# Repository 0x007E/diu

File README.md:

# `DIU` - Digital (Analog) Clock (Digitaluhr)

The `DIU` project is based on a pcb with an [ATtiny1606](#additional-information) a RTC [MCP7940](#additional-information) a USB/UART bridge [FT232RL](#additional-information) and a set of [74HC595](#additional-information) shift register. It can be used to display time and date on 84 `LEDs` that are mounted in 3 circles to the top pcb. The clock itself can be setup over UART and a terminal software ([e.g. TeraTerm](#additional-information)).

| Experience | Level |
|:------------|:-----:|
| Soldering   |  |
| Mechanical  |  |
| Software    |  |

# Downloads

| Type      | File               | Description              |
|:---------:|:------------------:|:-------------------------|
| Schematic | [pdf](https://github.com/0x007E/diu/releases/latest/download/schematic.pdf) / [cadlab](https://cadlab.io/project/28616/main/files) | Schematic files |
| Board | [pdf](https://github.com/0x007E/diu/releases/latest/download/pcb.pdf) / [cadlab](https://cadlab.io/project/28616/main/files) | Board file |
| Drill | [pdf](https://github.com/0x007E/diu/releases/latest/download/drill.pdf) | Drill file |
| PCB | [zip](https://github.com/0x007E/diu/releases/latest/download/kicad.zip) / [tar](https://github.com/0x007E/diu/releases/latest/download/kicad.tar.gz) | KiCAD/Gerber/BoM/Drill files |
| Mechanical | [zip](https://github.com/0x007E/diu/releases/latest/download/freecad.zip) / [tar](https://github.com/0x007E/diu/releases/latest/download/freecad.tar.gz) | FreeCAD/Housing and PCB (STEP) files     |
| Firmware | [zip](https://github.com/0x007E/diu/releases/latest/download/firmware.zip) / [tar](https://github.com/0x007E/diu/releases/latest/download/firmware.tar.gz) | Firmware for ATtiny1606 |
| Test-Firmware | [zip](https://github.com/0x007E/diu/releases/latest/download/test-firmware.zip) / [tar](https://github.com/0x007E/diu/releases/latest/download/test-firmware.tar.gz) | Test-Firmware for ATtiny1606 |

# Hardware

There are two parts of the hardware. The pcb and the housing of the `DIU`. The pcb is created with [KiCAD](#additional-information) and the housing with [FreeCAD](#additional-information). The software is programmed with [Microchip (Atmel) Studio](#additional-information). All files are built with `github actions` so that they are ready for a production environment. The housing is printed with a 3D-printer (`Dremel 3D40`).

## PCB

The circuit board is populated on both sides (Top, Bottom). The best way for soldering the `SMD` components is within a vapor phase soldering system and for the `THT` components with a standard soldering system. After placing and soldering the top parts, the board has to be cut off in the middle (white edge).

### Top Layer

### Bottom Layer

## Mechanical

The housing has a tolerance of `0.2mm` on each side of the case. So the pcb should fit perfectly in the housing. The tolerance can be modified with `FreeCAD` in the `Parameter` Spreadsheet. The corners of the circuit board need to be sanded a little.

### Assembled

#### Exploded

# Programming/Setup

The `DIU` can be powerd with `5V` from USB or an external source through connector `J1`. Over [UPDI](#additional-information) (`J3`) the `DIU` can be programmed with `avr-dude` or an [Microchip (Atmel) ICE](#additional-information) adapter. To setup the `DIU` it can be connected over USB to a computer and  configured with a terminal (e.g. [TeraTerm](#additional-information)) software. The firmware for the clock can be downloaded from the [download section](#downloads).

## FUSES

| Register  | Value  |
|:---------:|:------:|
| `WDTCFG`  | `0x00` |
| `BODCFG`  | `0x00` |
| `OSCCFG`  | `0x02` |
| `TCD0CFG` | `0x00` |
| `SYSCFG0` | `0xF5` |
| `SYSCFG1` | `0x00` |
| `APPEND`  | `0x00` |
| `BOOTEND` | `0x00` |

> To setup `RESET` (`PA0`) it is necessary to change the `SYSCFG0`-FUSE of the `ATtiny1606`. WARNING: To reset the `PA0` pin to `UPDI` mode a `12V` impulse is necessary to program the FUSES again.

# Firmware

The firmware of the `DIU` project can be downloaded and modified with [Microchip Studio](#additional-information). The software can be found in the [`./firmware`](./firmware/) directory and is splitted into different libraries. They can be found in the [./firmware/lib`](./firmware/lib/) folder. Feel free to modify the firmware to your own needings.

## Dataflow diagram

## UART Setup

To configure the `DIU` through UART (USB/UART bridge) a connection over USB to a computer and a terminal software (e.g. [Teraterm](#additional-information) is necessary. To start the setup the following settings need to be configured in the terminal. Then hit a key during init process in the terminal.

| Name      | Value  |
|:---------:|:------:|
| PORT      | COM?   |
| BAUD      | 9600   |
| DATABITS  | 8      |
| PARITY    | NONE   |
| STOPBITS  | 1      |
| FLOWCTRL  | NONE   |

### Connection setup

``` bash
# +--------------------------------------------------+
# |       ~------------------+                       |      +---------------------+
# |      ~  ATTINY 1606      |                       |      |                     |
# |     ~                  +-+-+                     |      | +-----------------+ |
# |    ~               VCC | 1 |          +----------+      | | TeraTerm        | |
# |      ~             PB0 | 2 |          |   U  +---+---+  | | ~~~~~~~~        | |
# |        ~           PB1 | 3 |          |   S  |  USB  |--+ | ~~~~~           | |
# |         ~    (TxD) PB2 | 4 +-----+    |   B  +---+---+  | | ~~~~~~~~~~~~    | |
# |        ~     (RxD) PB3 | 5 +--+  |    |   /      |      | |                 | |
# |       ~            GND | 6 |  |  |    |   U      |      | +-----------------+ |
# |     ~                  +-+-+  |  |    |   A      |      |                     |
# |    ~~~~~-----------------+    |  |  +-+-+ R      |      | Computer            |
# |                               |  +--+TxD| T      |      |                     |
# |  DDD   IIIIII UU  UU          +-----+RxD| +------+      +---------------------+
# |  D  D    II   UU  UU                +-+-+ |5V/3V3|
# |  D  D    II   UU  UU                  +----+-----+
# |  DDD   IIIIII  UUUU                              |
# +--------------------------------------------------+
```

### Enter configuration menu

To enter into the configuration mode it is necessary to press a `key` during startup.

The configuration starts and a menu to setup the `DIU` appears.

``` bash
# +------------------------------------------------+
# | System Configuration                           |
# +------------------------------------------------+
# | [1] Time and Date                              |
# | [2] Alarm                                      |
# | [3] Alarm Tone                                 |
# | [4] LED Intensity                              |
# | [5] Oscillator                                 |
# | [d] Discharge changes                          |
# | [q] Exit configuration                         |
# +------------------------------------------------+
# Input:
```

## TWI-Configuration

The `DIU` itself uses a `RTC` ([MCP7940](#additional-information)) with a power reserve (`battery`) to store the time. The `firmware` is connecte to the `RTC` over `TWI`. The twi configuration is stored in [`twi.h`](./firmware/lib/twi/twi.h) and the rtc configuration in [`mcp7940.h`](./firmware/lib/rtc/mcp7940.h) file.

### Connection between `ATtiny1606` and `MCP7940`

``` bash
# +----------------------------------------------------------------------------------------------------+
# |                               VCC VCC                                                              |
# |                                ^   ^                                                               |
# |                                |   |                                                               |
# |                             R +++ +++ R                                                            |
# |                             9 | | | | 1                                                            |
# |       ~------------------+  9 | | | | 0                                J                           |
# |      ~  ATTINY 1606      |    +++ +++ 0    +---------------------+     1    ~~~~~~                 |
# |     ~                  +-+-+   |   |     +-+-+                 +-+-+   8   ~  3   ~                |
# |    ~               VCC | X +---|---|-----+ 8 | VCC         BAT | 3 +--(X)-+   V    +------| GND    |
# |    ~         (SCL) PB0 | 0 +---+---|-----+ 6 | SCL             +-+-+       ~  0   ~                |
# |     ~        (SDA) PB1 | 1 +-------+-----+ 5 | SDA      M        |          ~~~~~~   C30           |
# |       ~            PB2 | 2 |             +-+-+          C      +-+-+                 ||            |
# |        ~           PB3 | 3 |           +-+ 5 | MFP      P   X! | 1 +----------+------||----| GND   |
# |         ~          PB4 | 4 |          /  +-+-+          7      +-+-+         ---     ||            |
# |         ~          PB5 | 5 |         /     |            9        |         +-----+                 |
# |        ~           PB6 | 6 |        /    +-+-+          4        |         |  Y1 | 32.768 kHz      |
# |       ~            GND | X +-------/-----+ 4 |          0        |         +-----+                 |
# |      ~                 +-+-+      /      +-+-+                 +-+-+         ---     ||            |
# |     ~                    |       /         |                X2 | 2 +----------+------||----| GND   |
# |     ~                  +-+-+    /          |                   +-+-+                 ||            |
# |      ~                 ~   ~   /           +---------------------+                   C31           |
# |       ~                ~   ~  /                                                                    |
# |        ~           PA7 | 7 +-+             DDD   IIIIII UU  UU                                     |
# |         ~              +-+-+               D  D    II   UU  UU                                     |
# |         ~                |                 D  D    II   UU  UU                                     |
# |        ~-----------------+                 DDD   IIIIII  UUUU                                      |
# +----------------------------------------------------------------------------------------------------+
```

### TWI Parameter

To read and save parameters in th `RTC` over `TWI` the bus is configured with the following setup:

| Parameter | Value   | Description     |
|:----------|:-------:|:----------------|
| Speed     | 400kHz  | Bus clock speed |

> Detail can be found [here](https://en.wikipedia.org/wiki/I%C2%B2C)

### RTC-Commands

``` c
             void mcp7940_init(RTC_Mode battery);
             void mcp7940_battery(RTC_Mode mode);
             void mcp7940_oscillator(RTC_Mode mode);

    unsigned char mcp7940_oscillator_value(void);
             void mcp7940_oscillator_copy(Copy_Mode mode);

       RTC_Status mcp7940_powerfail_status(void);
       RTC_Status mcp7940_oscillator_status(void);

      const char* mcp7940_weekday_string(unsigned char day);
    
    unsigned char mcp7940_hour(RTC_Data data);
    unsigned char mcp7940_minute(RTC_Data data);
    unsigned char mcp7940_second(void);

    unsigned char mcp7940_weekday(RTC_Data data);
    unsigned char mcp7940_day(RTC_Data data);
    unsigned char mcp7940_month(RTC_Data data);
    unsigned char mcp7940_year(void);
    unsigned char mcp7940_leapyear(void);

       RTC_Status mcp7940_setweekday(unsigned char weekday);
       RTC_Status mcp7940_settime(unsigned char hour, unsigned char minute, unsigned char second);
       RTC_Status mcp7940_setdate(unsigned char day, unsigned char month, unsigned char year);
       RTC_Status mcp7940_setoscillator(unsigned char trim);
```

## SPI-Configuration

The `firmware` itself is driving the LEDs over `SPI` through eleven [74HC595](#additional-information) shift registers. The spi configuration is stored in the [`clock.h`](./firmware/lib/clock/clock.h) and [`spi.h`](./firmware/lib/spi/spi.h) files.

### Connection between `ATtiny1606` and `74HC595`

``` bash
# +------------------------------------------------------------------------------------------------------+
# |                                     +----------------------------... ~ ...------------------------+  |
# |       ~------------------+         /            START(1)            ~             END(11)         |  | 
# |      ~  ATTINY 1606      |        /        +---------------+       ~         +---------------+    |  |
# |     ~                  +-+-+     /       +-+-+  74HC595  +-+-+    ~        +-+-+  74HC595  +-+-+  |  |
# |    ~               VCC | X +----/--------+ 16|    VCC    |16 |-.. ~ ....---+ 16|    VCC    |16 |  |  |
# |    ~               PA0 | 0 |   /         +---+           +-+-+     ~       +---+           +-+-+  |  |
# |     ~       (MOSI) PA1 | 1 +--/----------+ 14| SER    QH | 9 |--... ~ ...--+ 14| SER    QH | 9 +--+  |
# |       ~     (MISO) PA2 | 2 +-+           +---+           +-+-+       ~     +---+           +-+-+     |
# |        ~     (SCK) PA3 | 3 +-------------+ 11|   SRCLK   |11 |----... ~ ..-+ 11|   SRCLK   |11 |     |
# |         ~     (SS) PA4 | 4 +-------------+ 12|    RCLK   |12 |----... ~ ..-+ 12|    RCLK   |12 |     |
# |         ~  (CLEAR) PA5 | 5 +-------------+ 10|   SRCLR   |10 |---... ~ ...-+ 10|   SRCLR   |10 |     |
# |        ~  (OUTPUT) PA6 | 6 +-------------+ 13|     OE    |13 |--... ~ ...--+ 13|     OE    |13 |     |
# |       ~            GND | X +-------------+ 8 |    GND    | 8 |-... ~ ...---+ 8 |    GND    | 8 |     |
# |     ~                  +-+-+             +-+-+           +-+-+    ~        +-+-+           +-+-+     |
# |    ~~~~~-----------------+                 +--+~~~~~~~~~+--+      ~          +--+~~~~~~~~~+--+       |
# |                                               |         |          ~            |         |          |
# |  DDD   IIIIII UU  UU                         ---  LED  ---          ~          ---  LED  ---         |   
# |  D  D    II   UU  UU                         \ /       \ /           ~         \ /       \ /         |
# |  D  D    II   UU  UU                          |         |             ~         |         |          |
# |  DDD   IIIIII  UUUU                           |         |             ~         |         |          |
# +------------------------------------------------------------------------------------------------------+
```

### SPI Parameter

To control the LEDs through the shift registers over `SPI` the bus is configured with the following setup:

| Parameter | Value   | Description |
|:----------|:-------:|:------------|
| Clock     | F_CPU/4 | Bus clock speed is system speed divied by 4 |
| Direction | MSB     | MSB needs to be transmitted first |
| Polarity  | Rising  | Polarity of clock is rising `_/` |
| Phase     | Rising  | Data is valid when clock is rising `_/` |

> Detail can be found [here](https://de.wikipedia.org/wiki/Serial_Peripheral_Interface)

### SPI Frame

``` bash

# SPI display transmission
# _                                                SS                                                   _
#  \__________________________________________________~~~______________________________________________/
#                                                 SCK   
#     __    __    __    __    __    __    __    __       __    __    __    __    __    __    __    __    
# ___/1 \__/2 \__/3 \__/4 \__/5 \__/6 \__/7 \__/8 \__~~~/81\__/82\__/83\__/84\__/85\__/86\__/87\__/88\___
#                                                 MOSI
#    __    __    __    __    __    __    __    __       __    __    __    __    __    __    __    __
# __/H \__/O \__/U \__/R \__/  \__/  \__/  \__/  \__~~~/M \__/I \__/N \__/  \__/L3\__/L2\__/L1\__/L0\____
#   \__/  \__/  \__/  \__/  \__/  \__/  \__/  \__/     \__/  \__/  \__/  \__/  \__/  \__/  \__/  \__/
#    [7                   :                    0]    [7                   :                    0]
#
# L[3:0] ... LEDs on the backside of the pcb for signaling
```

### Clock-Commands

``` c
           void clock_init(void);
           void clock_output(CLOCK_Status status);
           void clock_clear(void);
   unsigned int clock_intensity(void);
    CLOCK_Error clock_setintensity(unsigned int intensity);
           void clock_copy_intensity(Copy_Mode mode);
    CLOCK_Error clock_settime(unsigned char hour, unsigned char minute, unsigned char second, CLOCK_Status_LED status);
    CLOCK_Error clock_setdate(unsigned char day, unsigned char month, CLOCK_Status_LED status);
           void clock_setdata(unsigned long data24, unsigned long long data60, CLOCK_Status_LED status);
           void clock_saveintensity(void);
```

# Additional Information

| Type       | Link               | Description              |
|:----------:|:------------------:|:-------------------------|
| ATtiny1606 | [pdf](http://ww1.microchip.com/downloads/en/DeviceDoc/ATtiny806_1606_Data_Sheet_40002029A.pdf) | ATtiny microcontroller |
| MPC7940 | [pdf](https://ww1.microchip.com/downloads/aemDocuments/documents/MPD/ProductDocuments/DataSheets/MCP7940N-Battery-Backed-I2C-RTCC-with-SRAM-20005010J.pdf) | Battery-Backed I2C Real-Time Clock/Calendar with SRAM |
| FT232RL | [pdf](https://ftdichip.com/wp-content/uploads/2020/08/DS_FT232R.pdf) | USB Full Speed to Serial UART IC, Includes Oscillator and EEPROM |
| 74HC595 | [pdf](https://www.ti.com/lit/ds/symlink/sn74hc595.pdf?) | 8-Bit Shift Registers With 3-State Output Registers |
| Atmel ICE | [pdf](https://ww1.microchip.com/downloads/en/DeviceDoc/Atmel-ICE_UserGuide.pdf) | Atmel ICE datasheet |
| UPDI | [web](https://github.com/0x007e/updi) | UPDI-Adapter with AVR-Dude |
| Microchip Studio | [web](https://www.microchip.com/en-us/tools-resources/develop/microchip-studio) | Download page for Microchip Studio |
| KiCAD | [web](https://www.kicad.org/) | KiCAD project page |
| FreeCAD | [web](https://www.freecad.org/) | FreeCAD project page |
| TeraTerm | [web](https://github.com/TeraTermProject/teraterm/releases/download/v5.3/teraterm-5.3.zip) | Terminal software for UART |

---

R. GAECHTER

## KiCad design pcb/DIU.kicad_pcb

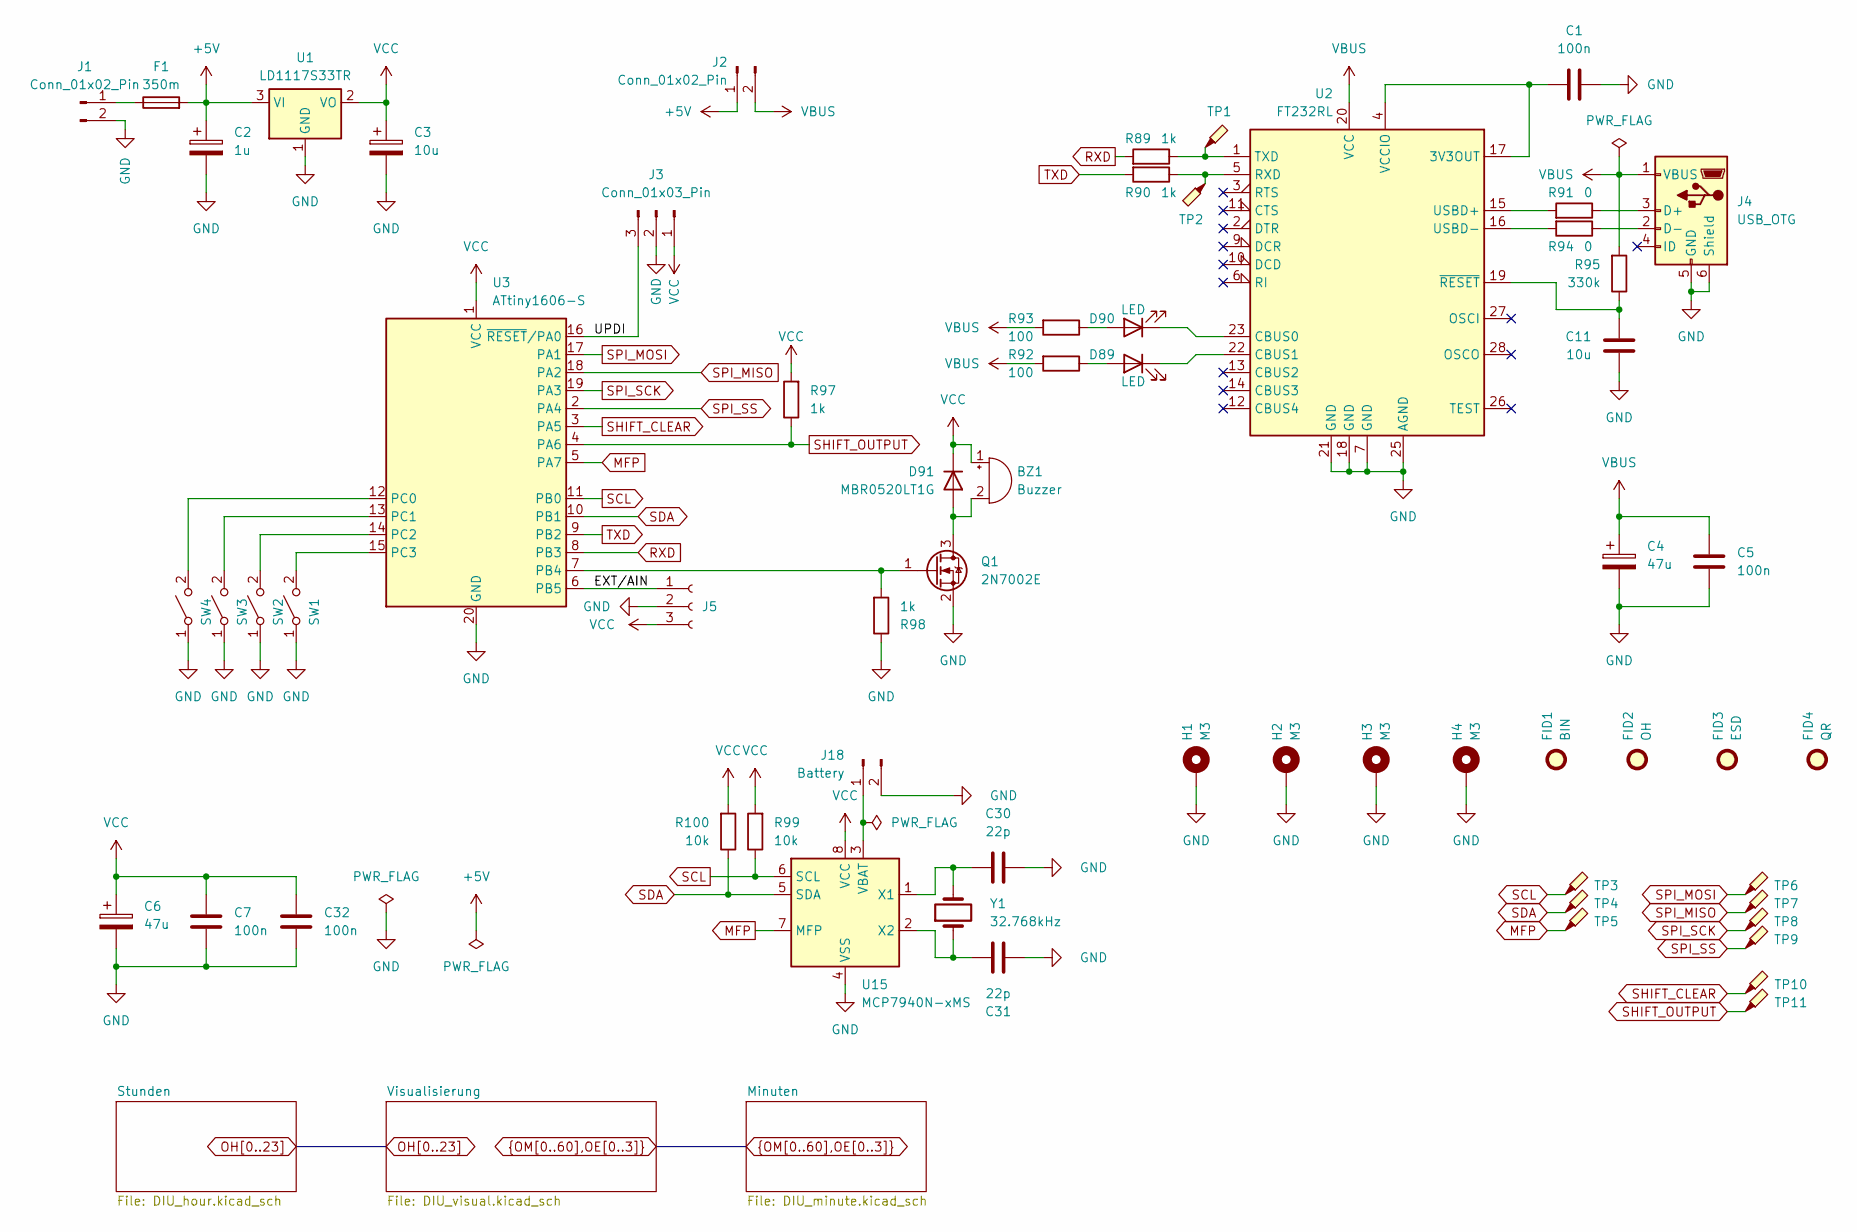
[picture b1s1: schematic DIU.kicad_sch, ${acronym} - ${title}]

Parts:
BZ1: Buzzer; MagneticBuzzer_ProSignal_ABT-410-RC
C1, C32: 100n; C_0603_1608Metric
C2: 1u; CP_EIA-3528-21_Kemet-B
C3: 10u; CP_EIA-6032-28_Kemet-C
C4, C6: 47u; CP_EIA-6032-15_Kemet-U
C5, C7: 100n; C_1206_3216Metric
C11: 10u; C_0603_1608Metric
C30, C31: 22p; C_0603_1608Metric
D89, D90: LED; LED_0603_1608Metric
D91: MBR0520LT1G; D_SOD-123
F1: 350m; Fuse_1206_3216Metric_Pad1.42x1.75mm_HandSolder
FID1: BIN; WEEE-Logo_4.2x6mm_SilkScreen
FID2: OH; OSHW-Logo2_7.3x6mm_SilkScreen
FID3: ESD; ESD-Logo_6.6x6mm_SilkScreen
FID4: QR; QR_0x007e
H1, H2, H3, H4: M3; MountingHole_3.2mm_M3_DIN965_Pad
J1, J2: Conn_01x02_Pin; PinHeader_1x02_P2.54mm_Vertical
J3: Conn_01x03_Pin; PinHeader_1x03_P2.54mm_Vertical
J4: USB_OTG; USB_Mini-B_Tensility_54-00023_Vertical
J5: Conn_01x03_Socket; PinSocket_1x03_P2.54mm_Vertical
J18: Battery; BatteryHolder_LINX_BAT-HLD-012-SMT
Q1: 2N7002E; SOT-23
R89, R90: 1k; R_0603_1608Metric
R91, R94: 0; R_0603_1608Metric
R92, R93: 100; R_0603_1608Metric
R95: 330k; R_0603_1608Metric
R97, R98: 1k; R_1206_3216Metric
R99, R100: 10k; R_0603_1608Metric
SW1, SW2, SW3, SW4: SW_SPST; SW_SPST_PTS645
TP1, TP2, TP3, TP4, TP5, TP6, TP7, TP8, TP9, TP10, TP11: TestPoint_Probe; TestPoint_Pad_D1.0mm
U1: LD1117S33TR; TO-263-2
U2: FT232RL; SSOP-28_5.3x10.2mm_P0.65mm
U3: ATtiny1606-S; SOIC-20W_7.5x12.8mm_P1.27mm
U15: MCP7940N-xMS; SOIC-8_3.9x4.9mm_P1.27mm
Y1: 32.768kHz; Crystal_SMD_3215-2Pin_3.2x1.5mm

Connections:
+5V: C2.1, F1.2, J2.1, U1.3 (VI)
/EXT/AIN: J5.1, U3.6 (PB5)
/UPDI: J3.3, U3.16 (~RESET/PA0)
GND: C1.2, C2.2, C3.2, C4.2, C5.2, C6.2, C7.2, C11.1, C30.2, C31.2, C32.2, H1.1, H2.1, H3.1, H4.1, J1.2, J3.2, J4.5 (GND), J4.6 (Shield), J5.2, J18.2, Q1.2 (S), R98.1, SW1.1 (A), SW2.1 (A), SW3.1 (A), SW4.1 (A), U1.1 (GND), U2.7 (GND), U2.18 (GND), U2.21 (GND), U2.25 (AGND), U3.20 (GND), U15.4 (VSS); also elsewhere on the board
MFP: TP5.1, U3.5 (PA7), U15.7 (MFP)
unnamed: BZ1.2 (-), D91.2 (A), Q1.3 (D)
unnamed: D89.2 (A), R92.1
unnamed: D89.1 (K), U2.22 (CBUS1)
unnamed: D90.2 (A), R93.1
unnamed: D90.1 (K), U2.23 (CBUS0)
unnamed: F1.1, J1.1
unnamed: J4.3 (D+), R91.1
unnamed: J4.2 (D-), R94.1
unnamed: J18.1, U15.3 (VBAT)
unnamed: Q1.1 (G), R98.2, U3.7 (PB4)
unnamed: SW1.2 (B), U3.15 (PC3)
unnamed: SW2.2 (B), U3.14 (PC2)
unnamed: SW3.2 (B), U3.13 (PC1)
unnamed: SW4.2 (B), U3.12 (PC0)
unnamed: C1.1, U2.4 (VCCIO), U2.17 (3V3OUT)
unnamed: R90.1, TP2.1, U2.5 (RXD)
unnamed: R89.1, TP1.1, U2.1 (TXD)
unnamed: R91.2, U2.15 (USBD+)
unnamed: R94.2, U2.16 (USBD-)
unnamed: C11.2, R95.1, U2.19 (~RESET)
unnamed: C30.1, U15.1 (X1), Y1.2
unnamed: C31.1, U15.2 (X2), Y1.1
RXD: R89.2, U3.8 (PB3)
SCL: R99.1, TP3.1, U3.11 (PB0), U15.6 (SCL)
SDA: R100.1, TP4.1, U3.10 (PB1), U15.5 (SDA)
SHIFT_CLEAR: TP10.1, U3.3 (PA5); also elsewhere on the board
SHIFT_OUTPUT: R97.1, TP11.1, U3.4 (PA6); also elsewhere on the board
SPI_MISO: TP7.1, U3.18 (PA2); also elsewhere on the board
SPI_MOSI: TP6.1, U3.17 (PA1); also elsewhere on the board
SPI_SCK: TP8.1, U3.19 (PA3); also elsewhere on the board
SPI_SS: TP9.1, U3.2 (PA4); also elsewhere on the board
TXD: R90.2, U3.9 (PB2)
VBUS: C4.1, C5.1, J2.2, J4.1 (VBUS), R92.2, R93.2, R95.2, U2.20 (VCC)
VCC: BZ1.1 (+), C3.1, C6.1, C7.1, C32.1, D91.1 (K), J3.1, J5.3, R97.2, R99.2, R100.2, U1.2 (VO), U3.1 (VCC), U15.8 (VCC); also elsewhere on the board

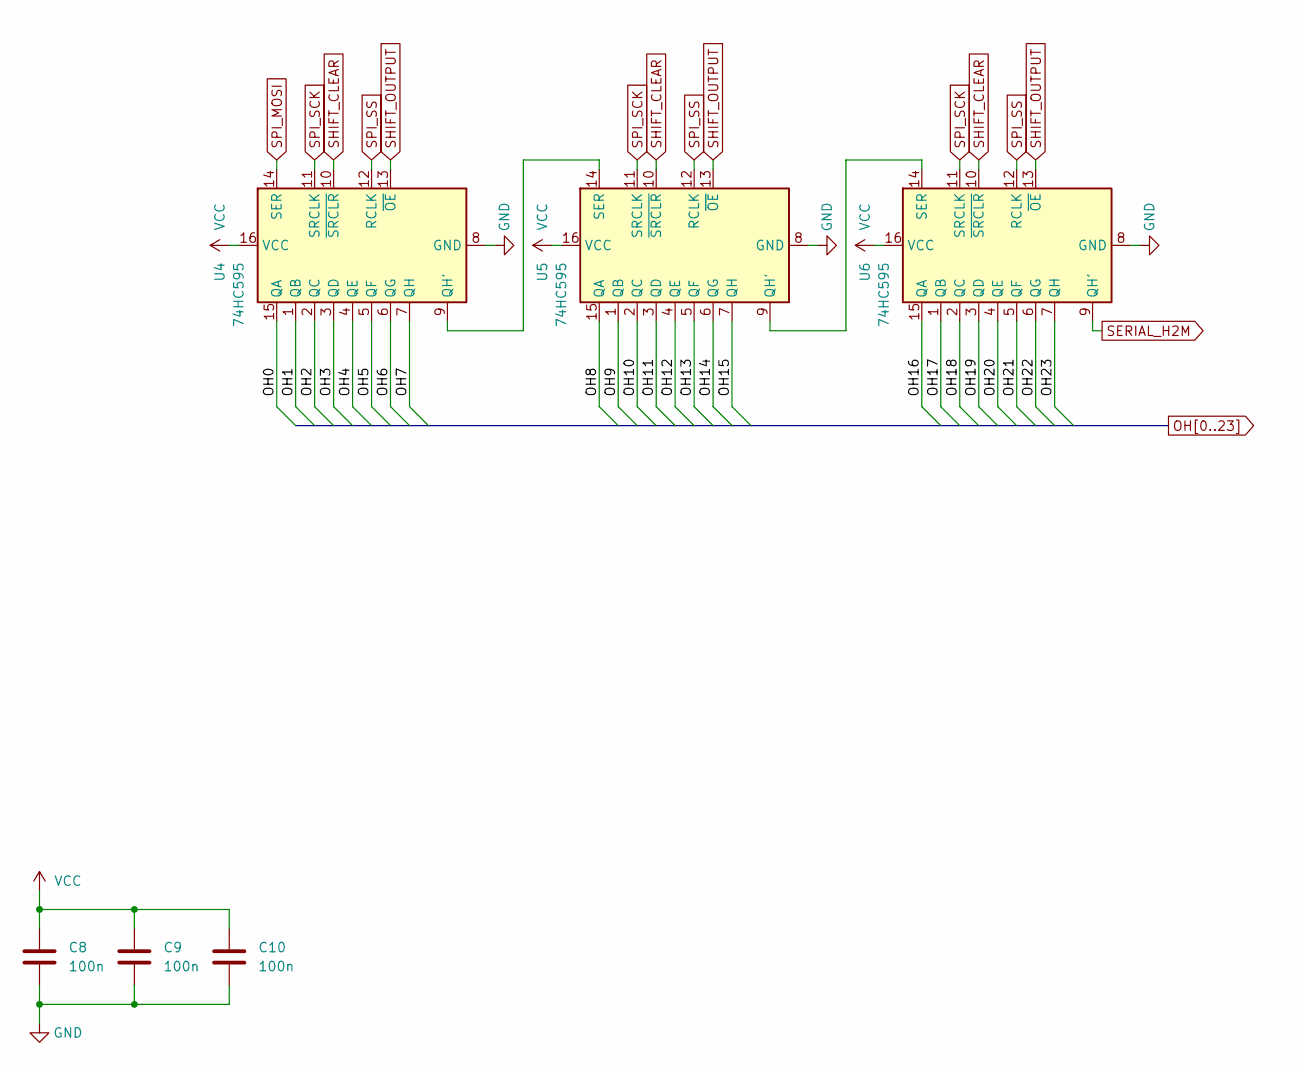
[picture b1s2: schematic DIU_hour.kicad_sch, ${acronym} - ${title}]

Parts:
C8, C9, C10: 100n; C_1206_3216Metric
U4, U5, U6: 74HC595; SOIC-16W_5.3x10.2mm_P1.27mm

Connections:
GND: C8.2, C9.2, C10.2, U4.8 (GND), U5.8 (GND), U6.8 (GND); also elsewhere on the board
unnamed: U4.9 (QH'), U5.14 (SER)
unnamed: U5.9 (QH'), U6.14 (SER)
OH0: U4.15 (QA); also elsewhere on the board
OH1: U4.1 (QB); also elsewhere on the board
OH2: U4.2 (QC); also elsewhere on the board
OH3: U4.3 (QD); also elsewhere on the board
OH4: U4.4 (QE); also elsewhere on the board
OH5: U4.5 (QF); also elsewhere on the board
OH6: U4.6 (QG); also elsewhere on the board
OH7: U4.7 (QH); also elsewhere on the board
OH8: U5.15 (QA); also elsewhere on the board
OH9: U5.1 (QB); also elsewhere on the board
OH10: U5.2 (QC); also elsewhere on the board
OH11: U5.3 (QD); also elsewhere on the board
OH12: U5.4 (QE); also elsewhere on the board
OH13: U5.5 (QF); also elsewhere on the board
OH14: U5.6 (QG); also elsewhere on the board
OH15: U5.7 (QH); also elsewhere on the board
OH16: U6.15 (QA); also elsewhere on the board
OH17: U6.1 (QB); also elsewhere on the board
OH18: U6.2 (QC); also elsewhere on the board
OH19: U6.3 (QD); also elsewhere on the board
OH20: U6.4 (QE); also elsewhere on the board
OH21: U6.5 (QF); also elsewhere on the board
OH22: U6.6 (QG); also elsewhere on the board
OH23: U6.7 (QH); also elsewhere on the board
SERIAL_H2M: U6.9 (QH'); also elsewhere on the board
SHIFT_CLEAR: U4.10 (~SRCLR), U5.10 (~SRCLR), U6.10 (~SRCLR); also elsewhere on the board
SHIFT_OUTPUT: U4.13 (~OE), U5.13 (~OE), U6.13 (~OE); also elsewhere on the board
SPI_MOSI: U4.14 (SER); also elsewhere on the board
SPI_SCK: U4.11 (SRCLK), U5.11 (SRCLK), U6.11 (SRCLK); also elsewhere on the board
SPI_SS: U4.12 (RCLK), U5.12 (RCLK), U6.12 (RCLK); also elsewhere on the board
VCC: C8.1, C9.1, C10.1, U4.16 (VCC), U5.16 (VCC), U6.16 (VCC); also elsewhere on the board

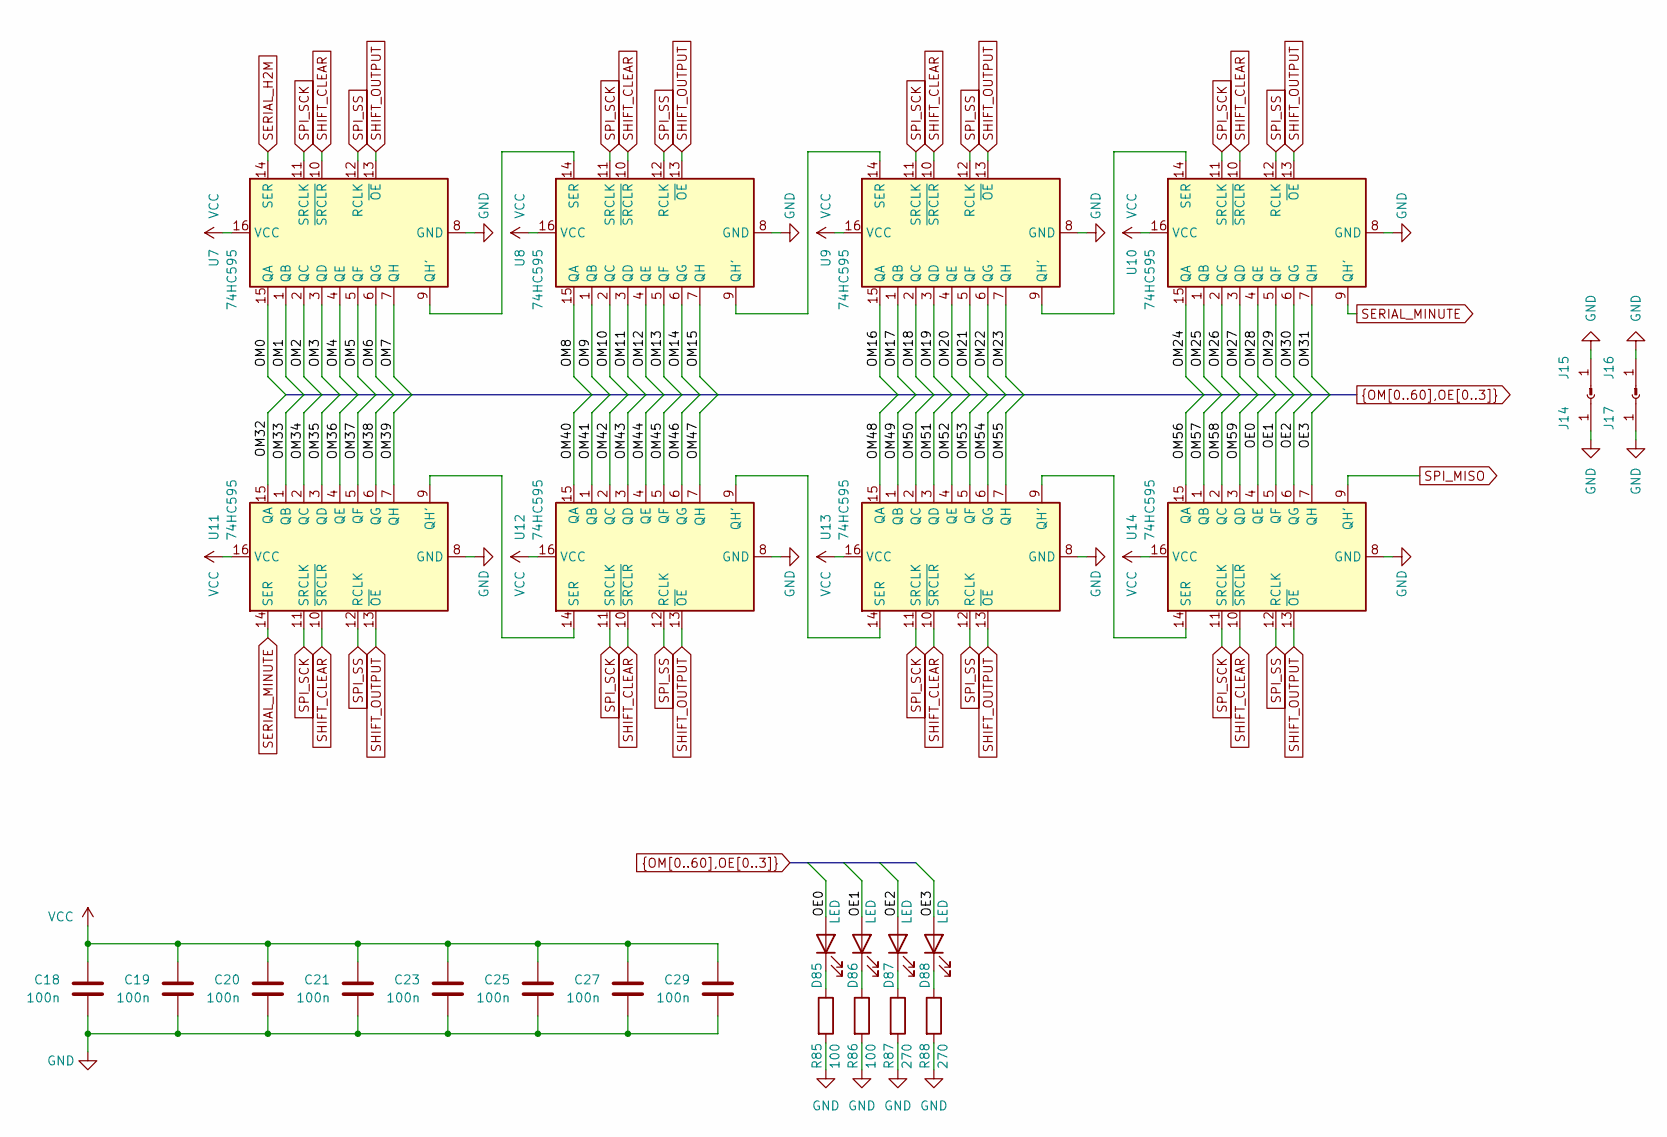
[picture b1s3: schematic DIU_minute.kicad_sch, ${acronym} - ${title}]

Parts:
C18, C19, C20, C21, C23, C25, C27, C29: 100n; C_1206_3216Metric
D85, D86, D87, D88: LED; LED_0603_1608Metric
J14, J17: Conn_01x01_Socket; PinSocket_1x01_P2.54mm_Vertical
J15, J16: Conn_01x01_Pin; PinHeader_1x01_P2.54mm_Vertical
R85, R86: 100; R_0603_1608Metric
R87, R88: 270; R_0603_1608Metric
U7, U8, U9, U10, U11, U12, U13, U14: 74HC595; SOIC-16W_5.3x10.2mm_P1.27mm

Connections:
GND: C18.2, C19.2, C20.2, C21.2, C23.2, C25.2, C27.2, C29.2, J14.1, J15.1, J16.1, J17.1, R85.2, R86.2, R87.2, R88.2, U7.8 (GND), U8.8 (GND), U9.8 (GND), U10.8 (GND), U11.8 (GND), U12.8 (GND), U13.8 (GND), U14.8 (GND); also elsewhere on the board
unnamed: D85.1 (K), R85.1
unnamed: D86.1 (K), R86.1
unnamed: D87.1 (K), R87.1
unnamed: D88.1 (K), R88.1
unnamed: U7.9 (QH'), U8.14 (SER)
unnamed: U8.9 (QH'), U9.14 (SER)
unnamed: U9.9 (QH'), U10.14 (SER)
unnamed: U11.9 (QH'), U12.14 (SER)
unnamed: U12.9 (QH'), U13.14 (SER)
unnamed: U13.9 (QH'), U14.14 (SER)
OE0: D85.2 (A), U14.4 (QE)
OE1: D86.2 (A), U14.5 (QF)
OE2: D87.2 (A), U14.6 (QG)
OE3: D88.2 (A), U14.7 (QH)
OM0: U7.15 (QA); also elsewhere on the board
OM1: U7.1 (QB); also elsewhere on the board
OM2: U7.2 (QC); also elsewhere on the board
OM3: U7.3 (QD); also elsewhere on the board
OM4: U7.4 (QE); also elsewhere on the board
OM5: U7.5 (QF); also elsewhere on the board
OM6: U7.6 (QG); also elsewhere on the board
OM7: U7.7 (QH); also elsewhere on the board
OM8: U8.15 (QA); also elsewhere on the board
OM9: U8.1 (QB); also elsewhere on the board
OM10: U8.2 (QC); also elsewhere on the board
OM11: U8.3 (QD); also elsewhere on the board
OM12: U8.4 (QE); also elsewhere on the board
OM13: U8.5 (QF); also elsewhere on the board
OM14: U8.6 (QG); also elsewhere on the board
OM15: U8.7 (QH); also elsewhere on the board
OM16: U9.15 (QA); also elsewhere on the board
OM17: U9.1 (QB); also elsewhere on the board
OM18: U9.2 (QC); also elsewhere on the board
OM19: U9.3 (QD); also elsewhere on the board
OM20: U9.4 (QE); also elsewhere on the board
OM21: U9.5 (QF); also elsewhere on the board
OM22: U9.6 (QG); also elsewhere on the board
OM23: U9.7 (QH); also elsewhere on the board
OM24: U10.15 (QA); also elsewhere on the board
OM25: U10.1 (QB); also elsewhere on the board
OM26: U10.2 (QC); also elsewhere on the board
OM27: U10.3 (QD); also elsewhere on the board
OM28: U10.4 (QE); also elsewhere on the board
OM29: U10.5 (QF); also elsewhere on the board
OM30: U10.6 (QG); also elsewhere on the board
OM31: U10.7 (QH); also elsewhere on the board
OM32: U11.15 (QA); also elsewhere on the board
OM33: U11.1 (QB); also elsewhere on the board
OM34: U11.2 (QC); also elsewhere on the board
OM35: U11.3 (QD); also elsewhere on the board
OM36: U11.4 (QE); also elsewhere on the board
OM37: U11.5 (QF); also elsewhere on the board
OM38: U11.6 (QG); also elsewhere on the board
OM39: U11.7 (QH); also elsewhere on the board
OM40: U12.15 (QA); also elsewhere on the board
OM41: U12.1 (QB); also elsewhere on the board
OM42: U12.2 (QC); also elsewhere on the board
OM43: U12.3 (QD); also elsewhere on the board
OM44: U12.4 (QE); also elsewhere on the board
OM45: U12.5 (QF); also elsewhere on the board
OM46: U12.6 (QG); also elsewhere on the board
OM47: U12.7 (QH); also elsewhere on the board
OM48: U13.15 (QA); also elsewhere on the board
OM49: U13.1 (QB); also elsewhere on the board
OM50: U13.2 (QC); also elsewhere on the board
OM51: U13.3 (QD); also elsewhere on the board
OM52: U13.4 (QE); also elsewhere on the board
OM53: U13.5 (QF); also elsewhere on the board
OM54: U13.6 (QG); also elsewhere on the board
OM55: U13.7 (QH); also elsewhere on the board
OM56: U14.15 (QA); also elsewhere on the board
OM57: U14.1 (QB); also elsewhere on the board
OM58: U14.2 (QC); also elsewhere on the board
OM59: U14.3 (QD); also elsewhere on the board
SERIAL_H2M: U7.14 (SER); also elsewhere on the board
SERIAL_MINUTE: U10.9 (QH'), U11.14 (SER)
SHIFT_CLEAR: U7.10 (~SRCLR), U8.10 (~SRCLR), U9.10 (~SRCLR), U10.10 (~SRCLR), U11.10 (~SRCLR), U12.10 (~SRCLR), U13.10 (~SRCLR), U14.10 (~SRCLR); also elsewhere on the board
SHIFT_OUTPUT: U7.13 (~OE), U8.13 (~OE), U9.13 (~OE), U10.13 (~OE), U11.13 (~OE), U12.13 (~OE), U13.13 (~OE), U14.13 (~OE); also elsewhere on the board
SPI_MISO: U14.9 (QH'); also elsewhere on the board
SPI_SCK: U7.11 (SRCLK), U8.11 (SRCLK), U9.11 (SRCLK), U10.11 (SRCLK), U11.11 (SRCLK), U12.11 (SRCLK), U13.11 (SRCLK), U14.11 (SRCLK); also elsewhere on the board
SPI_SS: U7.12 (RCLK), U8.12 (RCLK), U9.12 (RCLK), U10.12 (RCLK), U11.12 (RCLK), U12.12 (RCLK), U13.12 (RCLK), U14.12 (RCLK); also elsewhere on the board
VCC: C18.1, C19.1, C20.1, C21.1, C23.1, C25.1, C27.1, C29.1, U7.16 (VCC), U8.16 (VCC), U9.16 (VCC), U10.16 (VCC), U11.16 (VCC), U12.16 (VCC), U13.16 (VCC), U14.16 (VCC); also elsewhere on the board

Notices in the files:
README.md:
License CC By-NC-SA
License GPLv3
parts and their libraries:
license: CC BY-NC-SA 4.0
